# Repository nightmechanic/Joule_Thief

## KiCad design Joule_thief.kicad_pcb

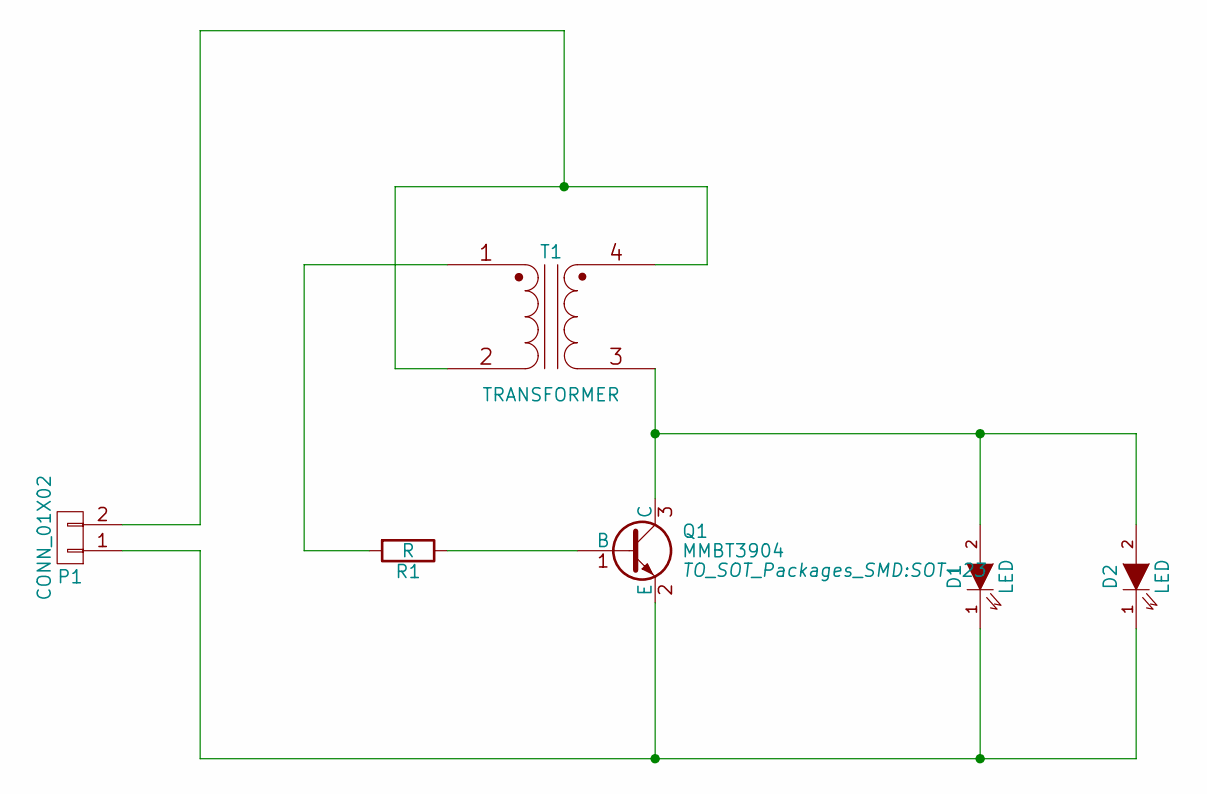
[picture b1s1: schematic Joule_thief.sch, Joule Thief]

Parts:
D1: LED; LED_5mm
D2: LED; LED_PLCC_2_HEATPAD
P1: CONN_01X02; conn_2_5mm
Q1: MMBT3904; SOT-23
R1: R; R_0805_HandSoldering
T1: TRANSFORMER; Transformer_22x10

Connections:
unnamed: D1.1 (K), D2.1 (K), P1.1, Q1.2 (E)
unnamed: D1.2 (A), D2.2 (A), Q1.3 (C), T1.3 (SA)
unnamed: P1.2, T1.2 (AB), T1.4 (SB)
unnamed: Q1.1 (B), R1.1
unnamed: R1.2, T1.1 (AA)

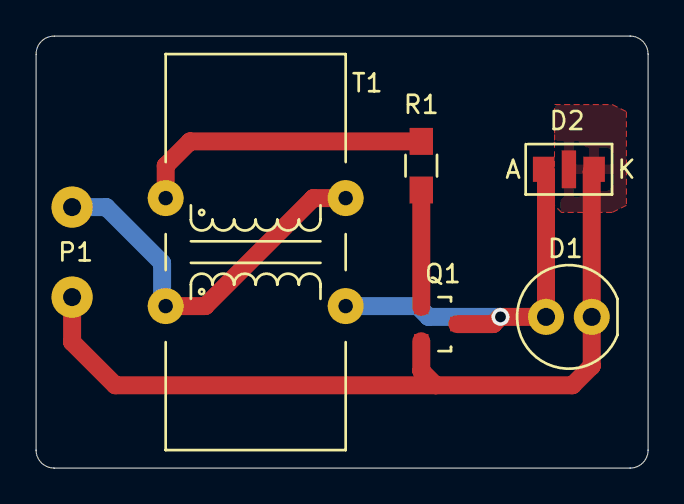
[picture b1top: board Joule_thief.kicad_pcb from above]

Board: 2 copper layers, 34.0 x 24.0 mm, 6 parts (0 on the bottom side), 5 nets.

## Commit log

2016-03-10 First version
2016-03-11 Added test points, improved layout
